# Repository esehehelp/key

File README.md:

# CH32X035 12キー USB キーパッド

`key.kicad_sch` の 4 行 × 3 列スイッチを読み取り、USB **HID Boot Keyboard** として入力するファームウェアです。CDC シリアルも複合デバイスのまま残し、参照実装と同じ 1200 bps touch → BootROM 書き込みを使用します。スケッチは `firmware/keypad/keypad.ino`、ボードパッケージは `hardware/key/ch32x035f7p6/` です。

## 配線とキー

| | col1 PA0 | col2 PA1 | col3 PA2 |
|---|---|---|---|
| row1 PA3 | SW1: 0 | SW5: 1 | SW9: 2 |
| row2 PA4 | SW2: 3 | SW6: 4 | SW10: 5 |
| row3 PA5 | SW3: 6 | SW7: 7 | SW11: 8 |
| row4 PA6 | SW4: 9 | SW8: A | SW12: B |

列は順番に LOW 駆動し、非選択列は高インピーダンス、行はプルアップ入力です。ダイオードは行側がアノード・列側がカソード。約 5 ms のデバウンス、最大 6 キー同時押し、8 byte Boot Keyboard レポートを使用します。0–9 は NumLock に依存しない通常の数字キー、A/B は英字キーです（大文字になるかはホストの Shift/Caps Lock 次第）。配列 `keys` を変更すれば HID Usage を変更できます。PC3 は操作しません。回路図では LED のカソードが VDD 側で逆方向のため、ソフトウェアだけでは点灯できません。PC18/19 の SWD、PC14–17 の USB には触れません。SW40 は USB D+ 側の回路、SW41 はリセットであり、キー配列には含みません。

## Arduino IDE / CLI

このリポジトリのボードパッケージは [ch32x035f7p6-micro-devboard](../ch32x035f7p6-micro-devboard) の Arduino コア・起動処理・GPIO・USB CDC・アップロードツールをコピーしたものです。**HID 複合デバイス対応だけ** `cores/arduino/ch32x_cdc.c` を拡張しています。通常の Micro Devboard ボードではなく、必ず **CH32X035F7P6 Keypad** を選択してください (FQBN `key:ch32x035f7p6:ch32x035f7p6`)。スケッチは追加の `.h` に依存せず、HID 送信関数を `.ino` 内で宣言します。ただし実装はこのボードコアにあるため、未導入ならこのリポジトリのボードパッケージをインストールしてください。USB ID は参照 CDC 専用版の 1A86:FE0C と区別して **1A86:FE0D** です（試作用 ID。製品化時は正規の VID/PID に変更すること）。

### Windows

1. このリポジトリをダウンロードして**展開**し、`setup.bat` をダブルクリックします。これだけでボード・GCC・wchisp・DLL をインストールします。既存ツールがあれば再利用し、不足分だけダウンロードします。参照ボードの古い `install.ps1` や削除済みブランチを使う必要はありません。`.ps1` だけダブルクリックしても実行されないので `setup.bat` を使用してください。
2. 完了/失敗の表示を確認します。スケッチブックが特殊な場所ならコマンドプロンプトから `setup.bat -Sketchbook D:\Arduino` を実行できます。Arduino IDE を再起動します。**初めて** WCH USB ISP で書き込む Windows マシンでは、別途 WCH の署名済み ISP ドライバが必要です（参照ボードの手順を参照）。すでに参照ボードを書き込めているなら不要です。
3. IDE でボード **CH32X035F7P6 Keypad** と CDC ポートを選択し、`firmware/keypad/keypad.ino` を開いて Verify / Upload します。CLI なら以下のコマンドを使えます。

### Linux

参照リポジトリの PlatformIO CH32 用 toolchain (`~/.platformio/packages/toolchain-riscv/bin`) と `wchisp` を用意し、`./install.sh` を実行します。インストール先は既定で `~/Arduino/hardware/key/ch32x035f7p6` です。別のスケッチブック・ツールチェインなら `./install.sh /path/to/sketchbook /path/to/toolchain/bin` と指定します。Python 3 と `wchisp` を PATH に配置してください。

```sh
arduino-cli compile --fqbn key:ch32x035f7p6:ch32x035f7p6 firmware/keypad
arduino-cli upload -p /dev/ttyACM0 --fqbn key:ch32x035f7p6:ch32x035f7p6 firmware/keypad
```

初回（CDC ファームウェア未書き込み）や BootROM 起動済みの場合は `-p none` でアップロードするか、参照ボードと同じ wch-link / WCH ISP の手順で初回書き込みを行ってください。実機の Arduino CLI 書き込み・検証と USB 複合デバイス列挙（cdc_acm / usbhid）を確認済みです。実キーの押下動作は未確認です。

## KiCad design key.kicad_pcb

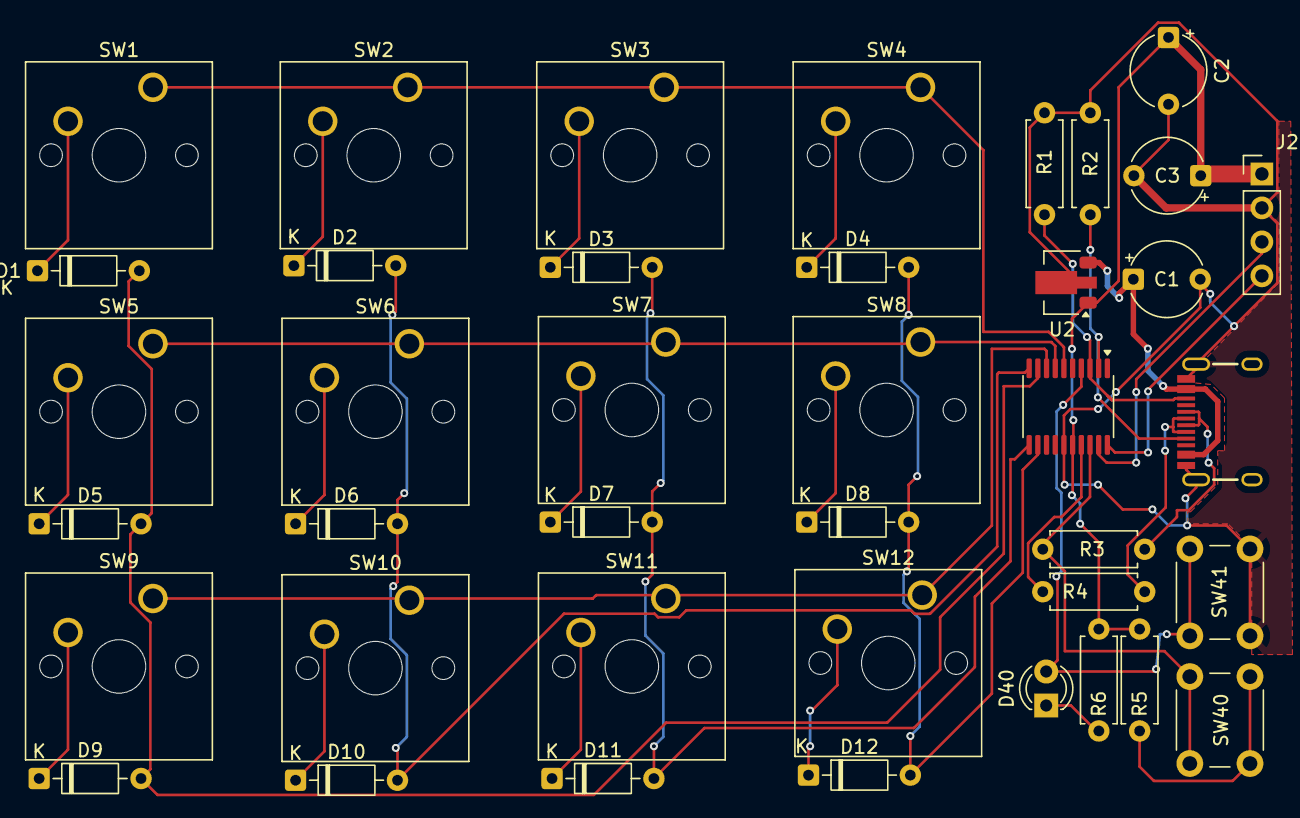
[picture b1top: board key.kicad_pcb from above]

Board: 2 copper layers, 40 parts (0 on the bottom side), 33 nets.

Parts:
C1, C2: 10u/35V; CP_Radial_Tantal_D5.5mm_P5.00mm
C3: 0.1u/50V; CP_Radial_Tantal_D5.5mm_P5.00mm
D1, D2, D3, D4, D5, D6, D7, D8, D9, D10, D11, D12: 1N4148; D_DO-35_SOD27_P7.62mm_Horizontal
D40: Red_LED; LED_D3.0mm
J1: USB_C_Receptacle; USB-C_16-HandSolder
J2: SWDIO; PinHeader_1x04_P2.54mm_Vertical
R1, R2, R5: 5k1; R_Axial_DIN0207_L6.3mm_D2.5mm_P7.62mm_Horizontal
R3, R4: 22; R_Axial_DIN0207_L6.3mm_D2.5mm_P7.62mm_Horizontal
R6: 1k; R_Axial_DIN0207_L6.3mm_D2.5mm_P7.62mm_Horizontal
SW1, SW2, SW3, SW4, SW5, SW6, SW7, SW8, SW9, SW10, SW11, SW12: SW_MEC_5G; SW_Cherry_MX_1.00u_PCB
SW40, SW41: EVPAWCD40; SW_PUSH_6mm
U1: CH32X035F7P6; TSSOP-20_4.4x6.5mm_P0.65mm
U2: NJM78L33SU3; SOT-89-3

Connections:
CC1: J1.A5 (CC1), R2.1, U1.2 (CC1/PC14)
CC2: J1.B5 (CC2), R1.1, U1.3 (CC2/PC15)
D+: R3.1, SW40.1, U1.18 (UDP/PC17)
D-: R4.1, U1.17 (UDM/PC16)
GND: C1.2, C2.2, C3.2, J1.GND, J1.S (SHIELD), J2.2, R1.2, R2.2, SW41.2, U1.15 (GND), U2.2 (GND)
unnamed: D1.1 (K), SW1.2 (A)
unnamed: D2.1 (K), SW2.2 (A)
unnamed: D3.1 (K), SW3.2 (A)
unnamed: D4.1 (K), SW4.2 (A)
unnamed: D5.1 (K), SW5.2 (A)
unnamed: D6.1 (K), SW6.2 (A)
unnamed: D7.1 (K), SW7.2 (A)
unnamed: D8.1 (K), SW8.2 (A)
unnamed: D9.1 (K), SW9.2 (A)
unnamed: D10.1 (K), SW10.2 (A)
unnamed: D11.1 (K), SW11.2 (A)
unnamed: D12.1 (K), SW12.2 (A)
unnamed: D40.1 (K), R6.1
unnamed: J1.A6 (D+), J1.B6 (D+), R3.2
unnamed: J1.A7 (D-), J1.B7 (D-), R4.2
unnamed: R5.1, SW40.2
PC3: D40.2 (A), SW41.1, U1.4 (NRST/PC3)
PC18: J2.3, U1.19 (SWDIO/PC18)
PC19: J2.4, U1.20 (SWCLK/PC19)
VBUS: C1.1, J1.VBUS, U2.3 (IN)
VDD: C2.1, C3.1, J2.1, R5.2, R6.2, U1.16 (VDD), U2.1 (OUT)
col1: SW1.1 (A), SW2.1 (A), SW3.1 (A), SW4.1 (A), U1.6 (PA0)
col2: SW5.1 (A), SW6.1 (A), SW7.1 (A), SW8.1 (A), U1.7 (PA1)
col3: SW9.1 (A), SW10.1 (A), SW11.1 (A), SW12.1 (A), U1.8 (PA2)
row1: D1.2 (A), D5.2 (A), D9.2 (A), U1.9 (PA3)
row2: D2.2 (A), D6.2 (A), D10.2 (A), U1.10 (PA4)
row3: D3.2 (A), D7.2 (A), D11.2 (A), U1.11 (PA5)
row4: D4.2 (A), D8.2 (A), D12.2 (A), U1.12 (PA6)

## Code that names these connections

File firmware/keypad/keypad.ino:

#include <Arduino.h>
#include <string.h>

// Implemented by this board core's CDC + HID composite USB driver.
extern "C" int ch32x_hid_send(const uint8_t report[8]);

// Schematic: SW1..4=col1 PA0, SW5..8=col2 PA1, SW9..12=col3 PA2.
// D1/D5/D9 anodes=row1 PA3; row2 PA4; row3 PA5; row4 PA6.
// Drive one column LOW at a time; all other columns are high impedance.
// Diode current flows from pulled-up row (anode) to selected column (cathode).
static const uint8_t cols[3] = {PA0, PA1, PA2};
static const uint8_t rows[4] = {PA3, PA4, PA5, PA6};
// USB HID keyboard usages: 0..9, A, B (top row digits, independent of NumLock).
static const uint8_t keys[4][3] = {
  {0x27, 0x1E, 0x1F}, // 0 1 2
  {0x20, 0x21, 0x22}, // 3 4 5
  {0x23, 0x24, 0x25}, // 6 7 8
  {0x26, 0x04, 0x05}  // 9 A B
};

static uint16_t stable, previous;
static uint8_t count[12];
static uint8_t last_sent[8];
static unsigned long last_scan, last_report;

static uint16_t scan_matrix() {
  uint16_t bits = 0;
  for (uint8_t c = 0; c < 3; ++c) {
    digitalWrite(cols[c], LOW);
    pinMode(cols[c], OUTPUT);
    delayMicroseconds(5);
    for (uint8_t r = 0; r < 4; ++r)
      if (digitalRead(rows[r]) == LOW) bits |= (uint16_t)1 << (r * 3 + c);
    pinMode(cols[c], INPUT); // never drive another column against this one
  }
  return bits;
}

void setup() {
  for (uint8_t r = 0; r < 4; ++r) pinMode(rows[r], INPUT_PULLUP);
  for (uint8_t c = 0; c < 3; ++c) pinMode(cols[c], INPUT);
}

void loop() {
  unsigned long now = millis();
  if ((unsigned long)(now - last_scan) < 1) return;
  last_scan = now;
  uint16_t raw = scan_matrix();
  for (uint8_t i = 0; i < 12; ++i) {
    uint16_t mask = (uint16_t)1 << i;
    if ((raw & mask) == (previous & mask)) {
      if (count[i] < 5) ++count[i];
    } else count[i] = 0;
    if (count[i] == 5) {
      if (raw & mask) stable |= mask;
      else stable &= ~mask;
    }
  }
  previous = raw;

  uint8_t report[8] = {0};
  uint8_t n = 0;
  for (uint8_t i = 0; i < 12; ++i)
    if ((stable & ((uint16_t)1 << i)) && n < 6)
      report[2 + n++] = keys[i / 3][i % 3];
  // Refresh on reconnection / lost transfers, including an all-released report.
  if (memcmp(report, last_sent, 8) || (unsigned long)(now - last_report) >= 250) {
    if (ch32x_hid_send(report)) {
      memcpy(last_sent, report, 8);
      last_report = now;
    }
  }
}
